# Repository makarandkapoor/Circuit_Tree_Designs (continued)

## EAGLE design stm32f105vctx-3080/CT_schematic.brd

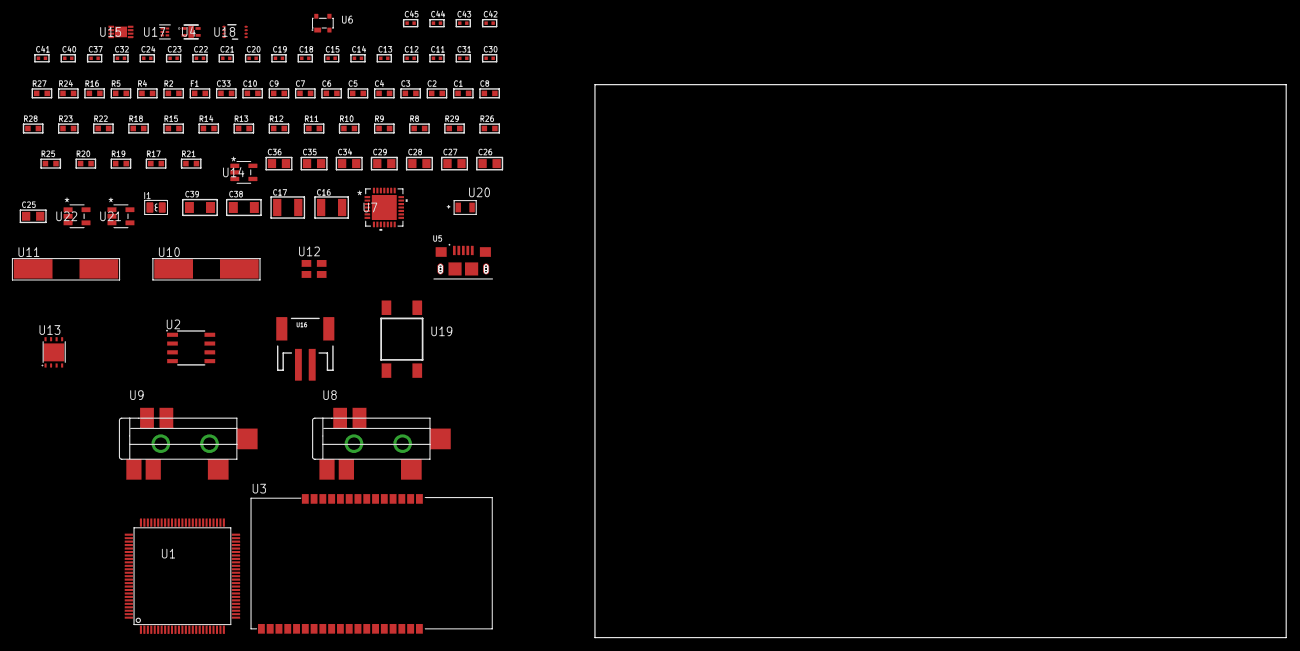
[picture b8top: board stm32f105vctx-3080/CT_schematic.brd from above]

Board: 2 copper layers, 122.6 x 80.0 mm, 94 parts (0 on the bottom side), 47 nets, no tracks yet.

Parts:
C1, C10, C33: 1e-06; C0603
C2, C3, C4, C5, C6, C7: 1e-07; C0603
C8: 4.7e-06; C0603
C9: 1e-08; C0603
C11, C12: 1e-11; C0402
C13, C32, C40, C42, C44, C45: 1e-08; C0402
C14, C15, C20, C21, C22, C23, C24, C37, C41, C43: 1e-07; C0402
C16, C17: 2.2e-05; C1210
C18, C19: 1e-09; C0402
C25, C26, C27, C28, C29, C34, C35, C36: 1e-05; C0805
C30, C31: 2.2e-11; C0402
C38, C39: 1e-05; C1206
F1: 240.0; L0603
I1: 1.5e-06; L0806
R2: 1000.0; R0603
R4, R5: 4700.0; R0603
R8, R9, R10, R11, R12, R22, R23, R28: 10000.0; R0603
R13, R14, R15: 47000.0; R0603
R16: 680.0; R0603
R17, R19: 100000.0; R0603
R18: 36000.0; R0603
R20: 220000.0; R0603
R21: 1000000.0; R0603
R24: 9100.0; R0603
R25: 680000.0; R0603
R26: 120000.0; R0603
R27: 2000.0; R0603
R29: 200000.0; R0603
U1: stm32f105vct6; LQFP100
U2: AT25080B-SSHL-T; SOIC-8
U3: ETRX3587
U4: Si7034-A10-IM; SI7034-A10-IM
U5: 10118193-0001LF; FCI_10118193-0001LF
U6: prtr5v0u2ax; SOT143B
U7: WM8731CLSEFL; QFN-28
U8, U9: SJ-43515TS-SMT-TR
U10: ABLS-25.000MHZ-B2F-T
U11: ABLS-12.288MHZ-B4-T
U12: ASEK-32.768KHz-ECST; ASEK
U13: LP2951ACSDX/NOPB; WSON-8
U14: ltc3406es5; TSOT-23-5
U15: MCP73831T-2ACI/MC; DFN8_2X3MC
U16: S2B-PH-SM4-TB(LF)(SN); JST-2-SMD
U17: TPS3895ADRYR; SON-6
U18: LSF0102DCTR; DCU0008A_N
U19: 4-1437565-2; SW_4-1437565-2
U20: Q65110A2395; LGM67K-G1J2-24-Z
U21, U22: nc7sz125m5x; NC7SZ125M5X

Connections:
CLK_CRYSTAL_U1_12: C11.1, U1.12, U10.1
CLK_CRYSTAL_U1_13: C12.1, U1.13, U10.2
CLK_CRYSTAL_U7_1: C30.1, U7.1, U11.1
CLK_CRYSTAL_U7_2: C31.1, U7.2, U11.2
CLK_U1_8: U1.8, U12.3
GND: C1.2, C2.2, C3.2, C4.2, C5.2, C6.2, C7.2, C8.2, C9.2, C10.2, C11.2, C12.2, C13.2, C14.2, C15.2, C19.2, C20.2, C21.2, C22.2, C23.2, C24.2, C25.2, C26.2, C27.2, C28.2, C29.2, C30.2, C31.2, C32.2, C33.2, C34.2, C35.2, C36.1, C36.2, C37.2, C38.2, C39.2, C40.2, C41.2, C42.2, C43.2, C44.2, C45.2, R2.2, R8.2, R12.2, R13.2, R14.2, R15.2, R19.2, R20.2, R24.2, R26.2, R27.2, U1.10, U1.19, U1.20, U1.27, U1.49, U1.74, U1.99, U2.4, U3.1, U3.13, U3.19, U3.20, U3.31, U3.33, U4.5, U5.5, U5.6, U5.7, U5.8, U5.9, U6.1, U7.4, U7.15, U7.19, U7.25, U7.26, U7.29, U8.1, U9.1, U12.2, U13.3, U13.4, U13.PAD, U14.2, U15.6, U15.9, U16.2, U17.2, U18.1, U20.C, U21.1, U21.3, U22.1, U22.3
INPUT_USBPOWER_5V: C38.1, R28.2, U1.68, U5.1, U6.4, U15.1, U15.2
NET_U1_14: R5.1, U1.14, U22.4
NET_U1_22: C9.1, C10.1, F1.1, U1.21, U1.22
NET_U1_94: R8.1, U1.94
NET_U1_98: U19.3, U19.4
NET_U2_3: R9.1, U2.3
NET_U2_7: R11.1, U2.7
NET_U3_7: R4.1, U3.7, U21.4
NET_U3_21: R12.1, U3.21
NET_U7_20: C24.1, C29.1, U7.20
NET_U8_2: C17.1, R14.1, U8.2
NET_U8_5: C16.1, R13.1, U8.5
NET_U9_5: C18.1, C19.1, R15.1, R16.1, U9.5
NET_U13_5: R17.1, U13.5
NET_U13_7: R18.2, R19.1, U13.7
NET_U14_3: I1.1, U14.3
NET_U14_5: R20.1, R21.1, U14.5
NET_U14_ATNET_3: I1.2, R21.2
NET_U15_5: R28.1, U15.5
NET_U15_8: R27.1, U15.8
NET_U17_1: R23.1, R24.1, U17.1
NET_U17_3: R25.2, R26.1, U17.3
NET_U17_4: R22.1, U17.4, U21.2, U22.2
NET_U18_8: R29.1, U18.8
NET_U19_1: R2.1, U19.1, U19.2
PROC_I2C1_SCL_TOXCVR: U4.2, U18.5
PROC_I2C1_SDA_TOXCVR: U4.4, U18.6
PROC_I2S2_CK: U1.52, U7.7
PROC_I2S2_SD: U1.54, U7.8
PROC_I2S2_WS: U1.51, U7.9, U7.11
PROC_SPI1_MISO: U1.31, U2.2
PROC_SPI1_MOSI: U1.32, U2.5
PROC_SPI1_NSS: R10.1, U1.29, U2.1
PROC_SPI1_SCK: U1.30, U2.6
PROC_UART4_RX: U1.79, U3.17
PROC_UART4_TX: U1.78, U3.18
PROC_USB_OTG_FS_DM: U1.70, U5.2, U6.3
PROC_USB_OTG_FS_DP: U1.71, U5.3, U6.2
VCC_S1_3V7: C33.1, C35.1, C39.1, U13.8, U14.4, U15.3, U15.4, U16.1
VCC_TIER1_1V8: C15.1, C20.1, C22.1, C23.1, C25.1, C27.1, C28.1, C34.1, C40.1, C41.1, C44.1, C45.1, R17.2, R18.1, R29.2, U4.1, U7.5, U7.12, U7.18, U13.1, U18.7, U21.5, U22.5
VCC_TIER1_3V3: C1.1, C2.1, C3.1, C4.1, C5.1, C6.1, C7.1, C8.1, C13.1, C14.1, C21.1, C26.1, C32.1, C36.2, C37.1, C42.1, C43.1, F1.2, I1.2, R4.2, R5.2, R9.2, R10.2, R11.2, R21.2, R22.2, R23.2, R25.1, U1.6, U1.11, U1.28, U1.50, U1.75, U1.100, U2.8, U3.32, U7.3, U12.4, U17.6, U18.2
